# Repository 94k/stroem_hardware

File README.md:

# ström
This repository contains the kicad and gerber files for the ström keyboard.
The PCB and plates are below 100mm x 100mm.
The ström is a split keyboard with 20 column staggered keys on each half.

## BOM
* 2 x Top plate
* 2 x PCB
* 2 x Bottom plate
* 2 x Pro Micro
* 2 x TRRS jack PJ-320D-A
* 1 x TRRS cable
* 40 x Cherry MX compatible switch
* 40 x 1N4148 Diode
* 40 x MX keycap
* 28 x M2x6 screw
* 14 x M2 spacer 11mm
* 8 x Rubber feet

The PCB supports through hole diodes as well as 0805 diodes.

## Assembly
The ström is assembled in a similar fashion as most sandwich style keyboards such as the [Let's Split](https://github.com/nicinabox/lets-split-guide) or the [Gherkin](https://imgur.com/a/O9p7n).
Unlike the Let's split however, the PCB is not invertible, instead it offers two potential footprints for the TRRS jack with the Pro Micro in between, the ström also doesn't require any jumper settings.
The Pro Micro is mounted with the USB towards the PCB on both sides to save space.

1. Solder all the diodes, you can solder them on the top or bottom side of the PCB.
2. Solder the pins/socket for the ProMicro
3. Put all the switches into the top plate. The holes are tight so make sure all the switches are level with the plate.
4. Put the switches with top plate on the PCB, it should be a snug fit.
5. Make sure no switch pins are bent, they should all go through the PCB.
6. Solder the two switches above the ProMicro.
7. Put tape over the ProMicro's USB port and solder or socket the ProMicro.
8. Flash the ProMicro and test the two soldered switches.
9. Solder the TRRS jack to one of the two footprints.
10. Solder the rest of the switches.
11. Put in the screws and spacers, screw in the bottom plate.
12. Flash both sides at least once, you only have to flash the master when you update your keymap in the future.

By default the ström uses the QMK serial connection to communicate between the two halves, although either I2C support or shared RGB backlighting can be added.

### Notes
* TRRS shorts contacts while plugging and unplugging. *Never plug or unplug the TRRS cable while USB is connected.*
* The ProMicro's USB port is close to the solder joint of the switch above, use mask tape or similar over the port to avoid a short.
* If you plan on socketing your ProMicros you may need longer spacers.
* Some diode footprints are very close together, try to avoid solder bridges or use SMD diodes.
* J1 is close to the switch footprint next to it, solder the TRRS jack first.
* You should be able to use 10mm spacers instead of 11mm, although 11mm give you some more room to work with and are recommended.

### I2C
I2C has not been tested but should generally be working, follow the instructions below.

In order to use I2C, Pin 2 (SDA) on the Pro Micro has to be connected to the dormant trace in the TRRS connection, a pad to do so is provided as "DT2" right next to Pin 2, simply jump from the pin to the pad with a short wire.

Additionally I2C requires a 4.7kΩ pull-up resistor to each data line, the best place to add them is one of the empty TRRS jack footprints.
VCC is connected to the right topmost pad, below is DT2 and the other data trace DT1 is the bottommost pad on that side, the single pad on the left side is GND.
Simply use a SMD resistor between VCC and DT2 and solder the legs of a through hole resistor between VCC and DT2.

### RGB backlighting
Use a 3 trace RGB strip, tap DT2, VCC and GND to propagate the color to the other half. Use either pin 9 or pin 10 on the pro micro as RGB pin.

## Flashing

The ström [supports QMK](https://github.com/94k/stroem_firmware).
You can use a flat screw driver to short RST and GND instead of soldering a switch on SW1.

## Todo
* Move diode footprints to provide more space for soldering.
* Rotate some of the keys to provide more space for the TRRS jacks and the USB port.
* Replace TRRS jacks with 5pin Micro USB for I2C *and* backlight.
* Add M2 holes to PCB for plateless builds.
* Reduce size of PCB and plates.
* Provide footprints for I2C resistors.
* Provide jumper footprints for backlighting (master/slave).
* Add ICSP headers.

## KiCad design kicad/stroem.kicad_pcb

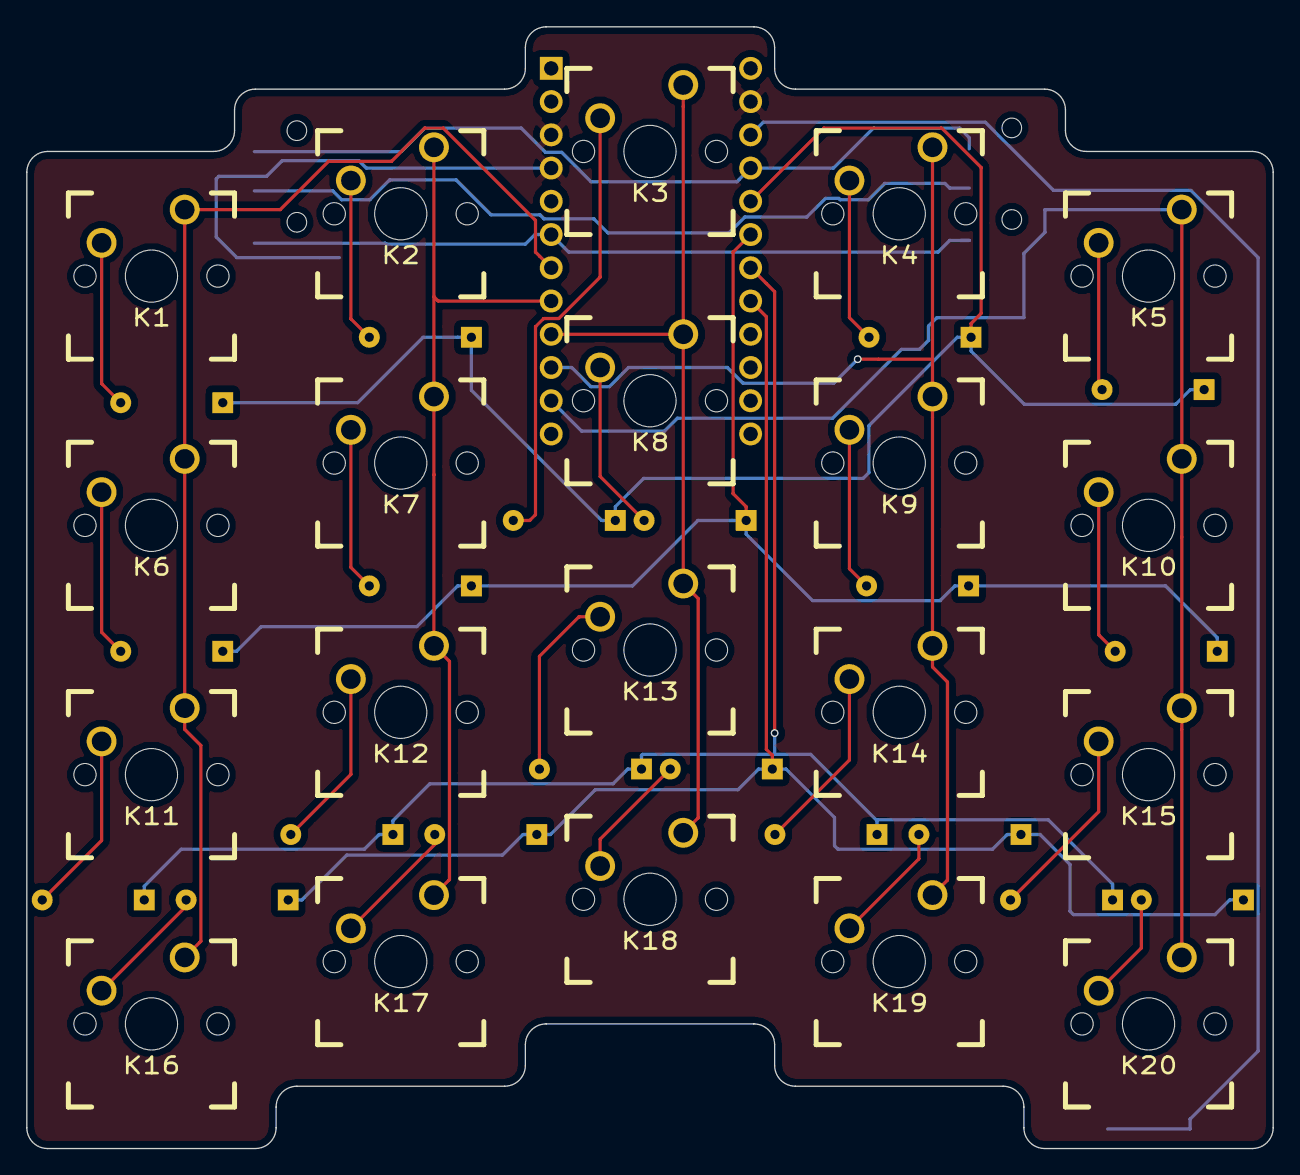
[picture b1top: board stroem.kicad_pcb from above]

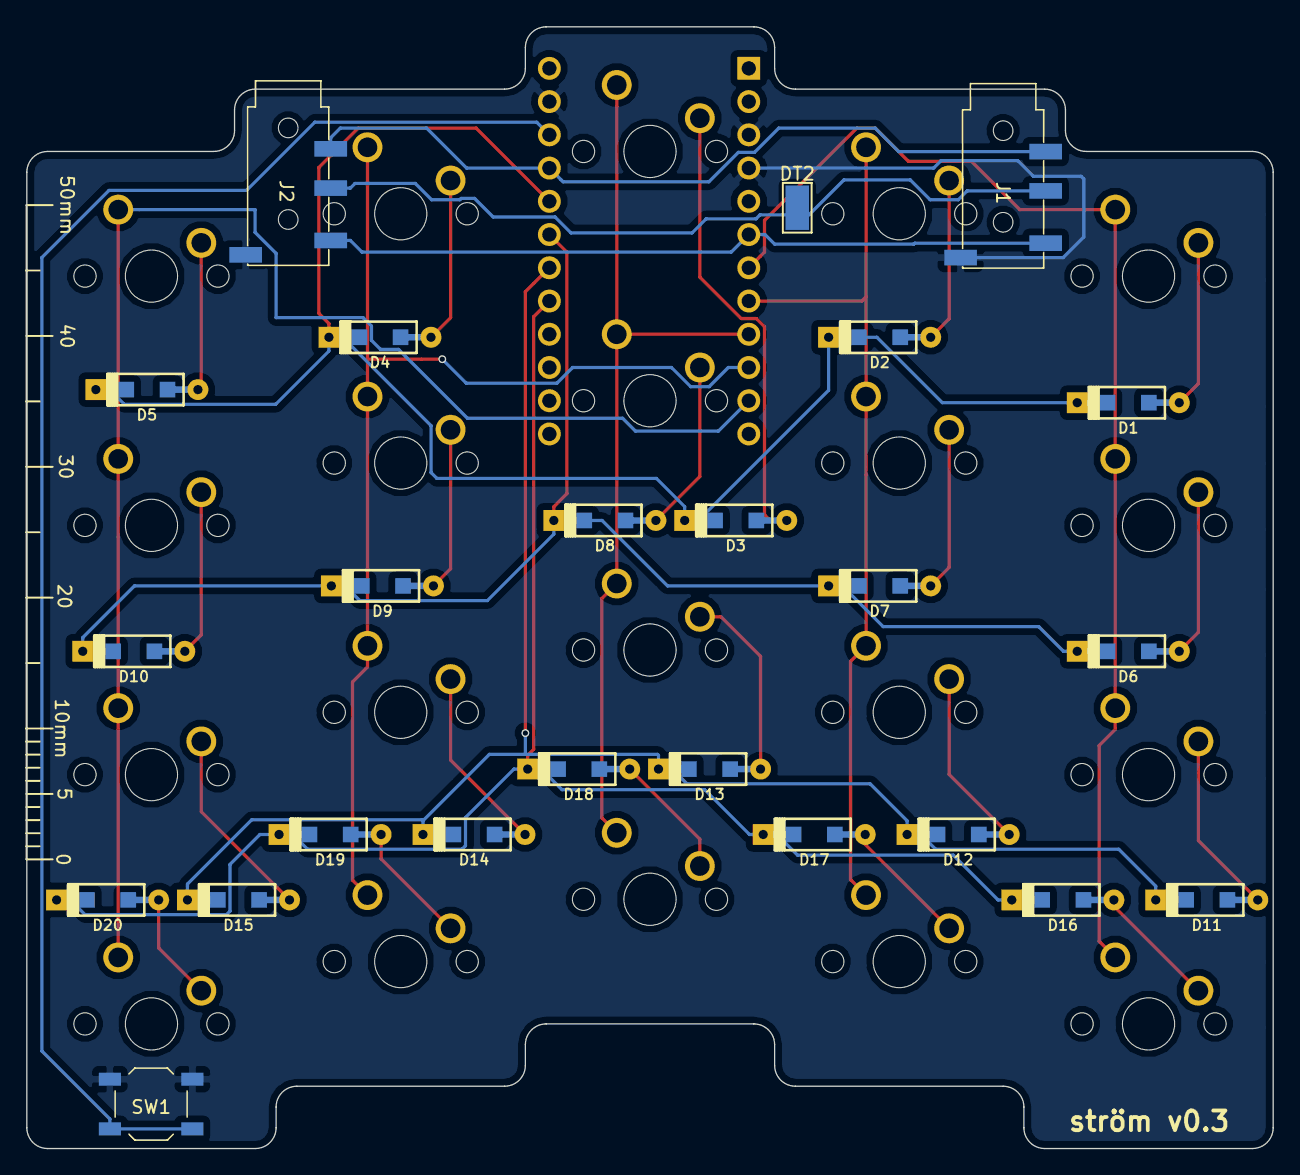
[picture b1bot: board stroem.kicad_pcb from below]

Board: 2 copper layers, 95.3 x 85.7 mm, 45 parts (24 on the bottom side), 34 nets.

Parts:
D1, D2, D3, D4, D5, D6, D7, D8, D9, D10, D11, D12, D13, D14, D15, D16, D17, D18, D19, D20: D; D_SOD123_axial
DT2: TEST; Test_Point_Keystone_5015_Micro-Minature
J1, J2: Audio-Jack-4; PJ320D_3.5mm_Jack
K1, K2, K3, K4, K5, K6, K7, K8, K9, K10, K11, K12, K13, K14, K15, K16, K17, K18, K19, K20: KEYSW; CHERRY_PCB_100H
SW1: SW_Push; SW_SPST_TL3342
U1: ProMicro; Pro_Micro_fixed

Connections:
/C0: K1.1, K6.1, K11.1, K16.1, U1.7
/C1: K2.1, K7.1, K12.1, K17.1, U1.8
/C2: K3.1, K8.1, K13.1, K18.1, U1.9
/C3: K4.1, K9.1, K14.1, K19.1, U1.10
/C4: K5.1, K10.1, K15.1, K20.1, U1.11
/R0: D1.1, D2.1, D3.1, D4.1, D5.1, U1.20
/R1: D6.1, D7.1, D8.1, D9.1, D10.1, U1.19
/R2: D11.1, D12.1, D13.1, D14.1, D15.1, U1.18
/R3: D16.1, D17.1, D18.1, D19.1, D20.1, U1.17
GND: J1.4, J2.4, SW1.2, U1.3, U1.4, U1.23
unnamed: D1.2, K1.2
unnamed: D2.2, K2.2
unnamed: D3.2, K3.2
unnamed: D4.2, K4.2
unnamed: D5.2, K5.2
unnamed: D6.2, K6.2
unnamed: D7.2, K7.2
unnamed: D8.2, K8.2
unnamed: D9.2, K9.2
unnamed: D10.2, K10.2
unnamed: D11.2, K11.2
unnamed: D12.2, K12.2
unnamed: D13.2, K13.2
unnamed: D14.2, K14.2
unnamed: D15.2, K15.2
unnamed: D16.2, K16.2
unnamed: D17.2, K17.2
unnamed: D18.2, K18.2
unnamed: D19.2, K19.2
unnamed: D20.2, K20.2
unnamed: J1.1, J2.1, U1.5
unnamed: DT2.1, J1.2, J2.2
unnamed: SW1.1, U1.22
VCC: J1.3, J2.3, U1.21

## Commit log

2018-05-08 Update LICENSE
2018-05-09 Create LICENSE
2018-05-11 added image
2018-09-04 improved readme
